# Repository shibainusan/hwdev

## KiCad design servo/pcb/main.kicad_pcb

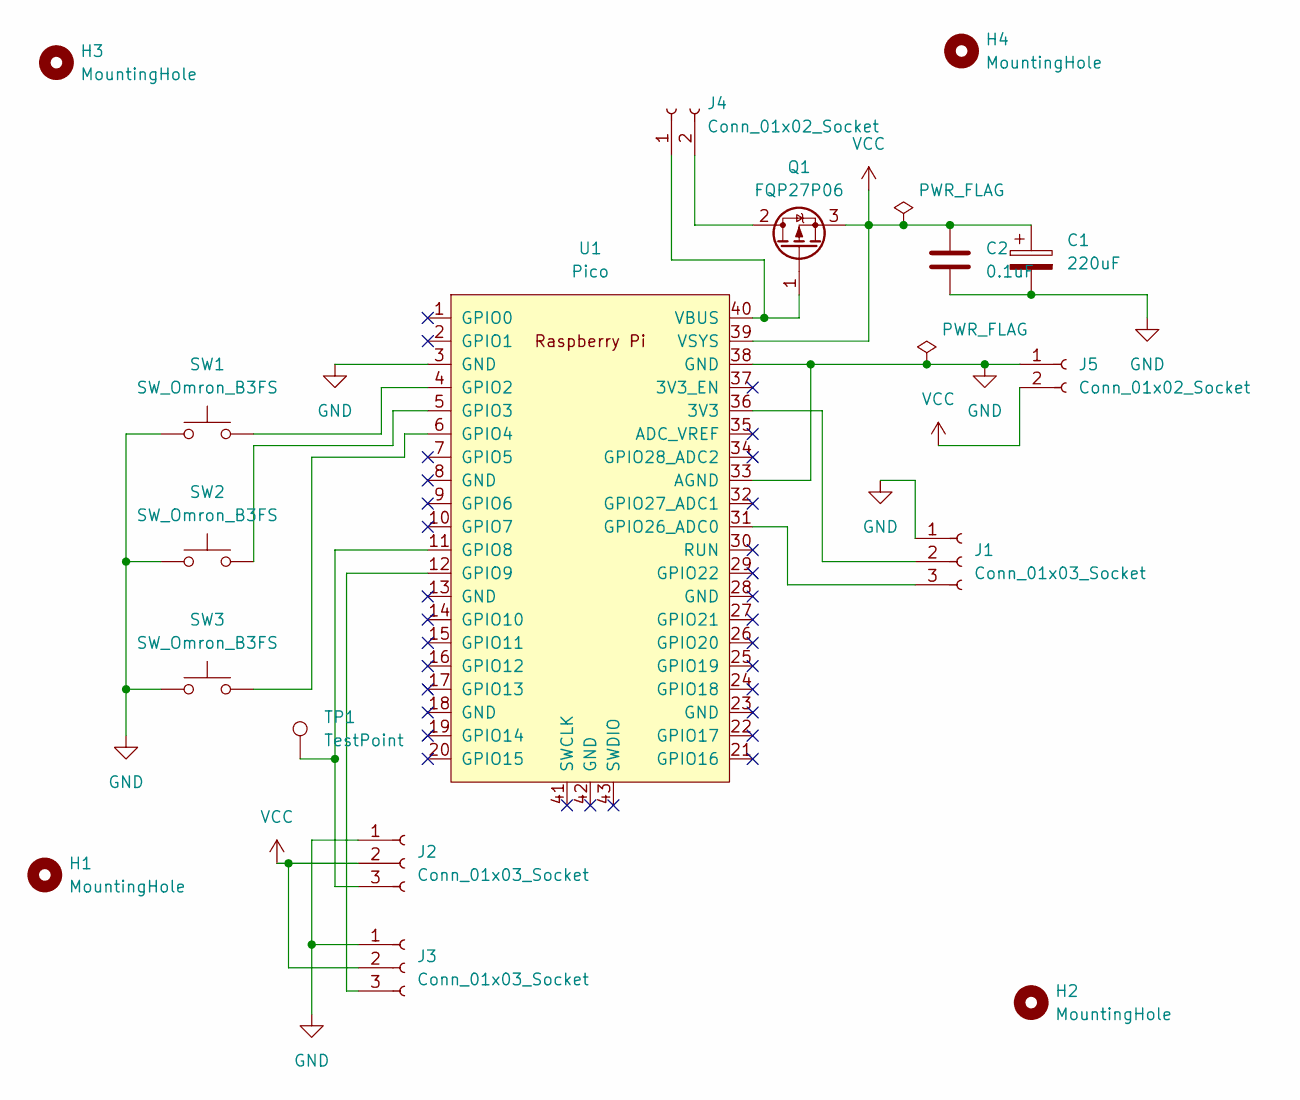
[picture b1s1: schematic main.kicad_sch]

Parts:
C1: 220uF; CP_Radial_D5.0mm_P2.50mm
C2: 0.1uF; C_Disc_D3.0mm_W2.0mm_P2.50mm
H1, H2, H3, H4: MountingHole; MountingHole_3.2mm_M3
J1, J2, J3: Conn_01x03_Socket; PinSocket_1x03_P2.54mm_Vertical
J4, J5: Conn_01x02_Socket; PinSocket_1x02_P2.54mm_Vertical
Q1: FQP27P06; TO-92_Inline_Wide
SW1, SW2, SW3: SW_Omron_B3FS; SW_PUSH_6mm
TP1: TestPoint; TestPoint_THTPad_D2.0mm_Drill1.0mm
U1: Pico; RPi_Pico_SMD_TH

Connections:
GND: C1.2, C2.2, J1.1, J2.1, J3.1, J5.1, SW1.1, SW2.1, SW3.1, U1.3 (GND), U1.33 (AGND), U1.38 (GND)
unnamed: J1.2, U1.36 (3V3)
unnamed: J1.3, U1.31 (GPIO26_ADC0)
unnamed: J2.3, TP1.1, U1.11 (GPIO8)
unnamed: J3.3, U1.12 (GPIO9)
unnamed: J4.1, Q1.1 (G), U1.40 (VBUS)
unnamed: J4.2, Q1.2 (D)
unnamed: SW1.2, U1.4 (GPIO2)
unnamed: SW2.2, U1.5 (GPIO3)
unnamed: SW3.2, U1.6 (GPIO4)
VCC: C1.1, C2.1, J2.2, J3.2, J5.2, Q1.3 (S), U1.39 (VSYS)

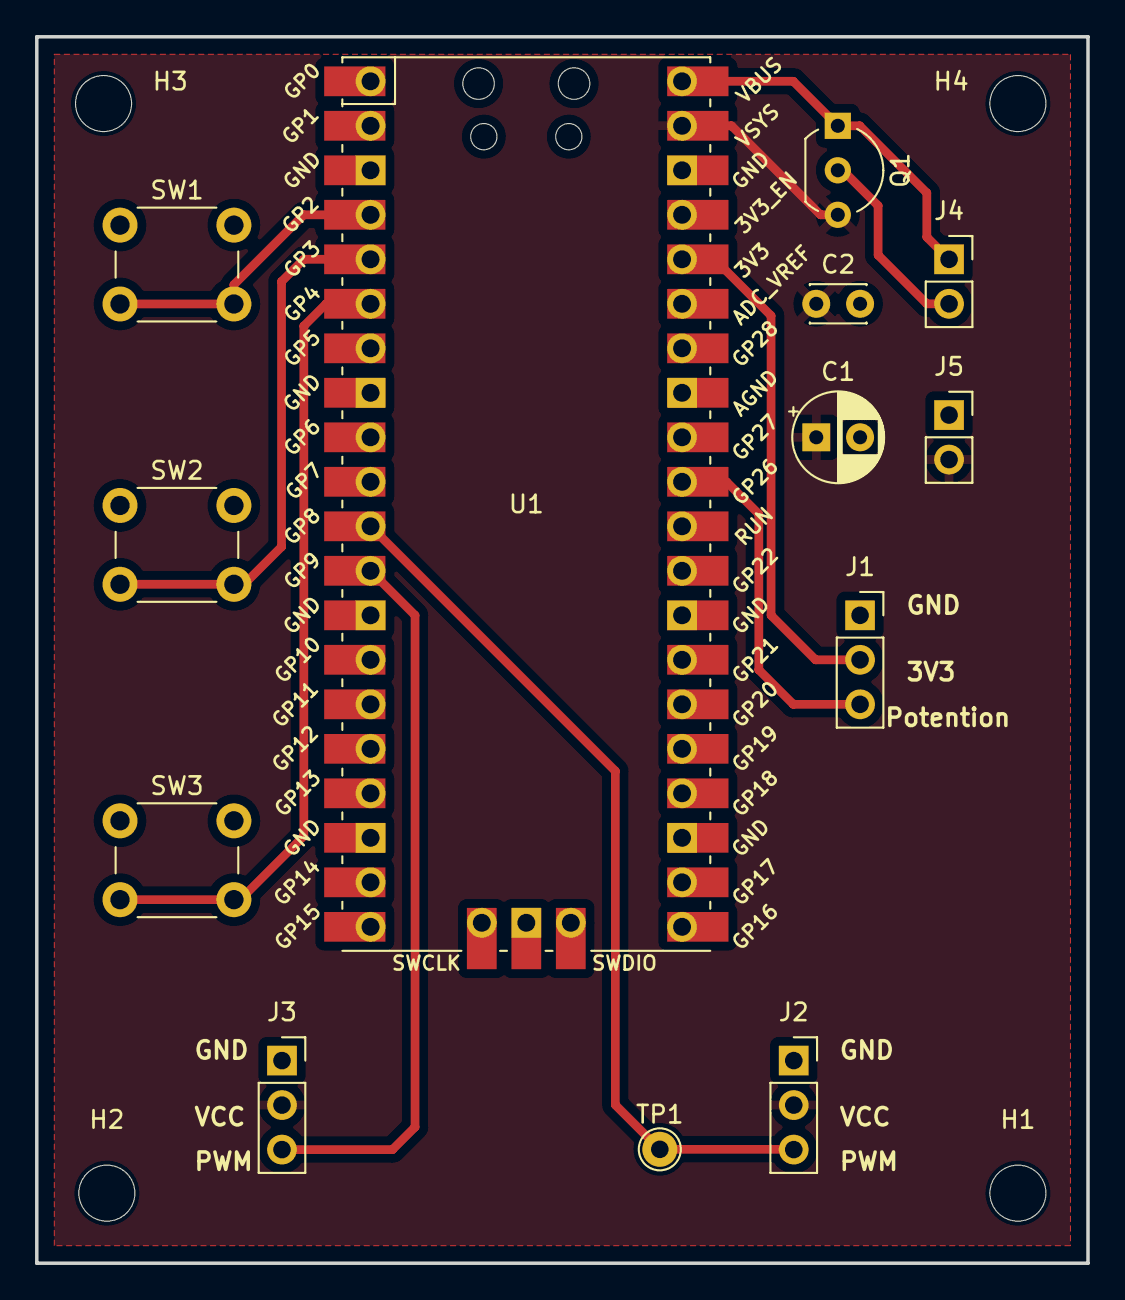
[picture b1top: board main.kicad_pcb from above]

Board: 2 copper layers, 60.0 x 70.0 mm, 17 parts (0 on the bottom side), 11 nets.

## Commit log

2017-05-05 old projects
2017-05-05 usb switcher
2017-05-05 working
2017-05-06 CRLF was not removed correctly.
2017-05-06 1st release
2017-05-06 power source board with 5V and DC-DC stepdown converter output.
2017-06-17 replaced to N MOS FET
2023-11-07 4 port SMA switcher Arduino FW and schematics
2023-11-08 Case
2023-11-09 OpenScad
2023-11-09 https://github.com/BelfrySCAD/BOSL2/archive/refs/heads/master.zip
2023-11-09 Arduino基板が入らないので天井上げ ねじ穴を皿ネジに
2023-11-09 sidepanel
2023-11-11 Portずらし対応
2023-11-18 initial
2023-11-19 高さが10cm超えるので無理やり
2023-11-19 FANねじ止め箇所が浮く問題修正
2023-11-19 back/Front panel長さ調整
2023-11-27 コマンド対応 ファンガードの穴拡大
2023-12-10 穴位置調整
2023-12-14 回転軸のクリアランスが小さすぎて回転が渋い ハウジング内側ねじ穴が回転軸と干渉する サーボ取り付けねじ穴が浅い
2023-12-17 servo軸を直接マウントできないぽい。
2023-12-22 Servoハウジング頭 Servo固定
2023-12-22 シリコン抑え
2023-12-23 サーボ取り付けホイールの真ん中にねじ穴逃げを設置 M2ビスの効きがわるいので受け穴を1.8mm-->1.6mmに縮小
2023-12-25 トップカバー穴あけ
2023-12-27 LR逆回転モード追加
2023-12-28 実体配線簡略化のためにServo制御ピン変更
2023-12-28 操作パネル
2023-12-28 一体成型やめ。面で出して接着する。
2023-12-30 speed選択可能幅拡大
2023-12-31 内部演算を角度センターを0、範囲±90度で計算するようにした
2023-12-31 サーボ直取り付けホーン
2023-12-31 サーボにハマるようになった。ねじはM2。
2024-01-01 attachment受け径拡大。30->32mm
2024-01-01 固定できた
2024-01-01 attachment受け径拡大につきカップ抑えも+2mm拡大
2024-01-06 Controlケースを一体成型とパーツ接着組み立てで分離
2024-01-07 P配線した
2024-01-07 rev1
2024-01-14 足を追加
2024-01-14 Added sleep mode.
2024-01-21 P板むけ変更
2024-01-21 tpuとplaで分けた
2024-01-23 サイズ調整
2024-01-27 added rp2040 dormant mode. https://github.com/matthias-bs/arduino-pico-sleep
2024-02-24 unblock ClientConnectThread
2024-02-24 readable log
2024-02-24 Send WoL Magic packet
2024-02-26 Local TCP sessionが切れると無限ループになる問題修正
2024-02-26 implementing local commands.
2024-02-27 Add local commands
2024-02-27 Leave log when local command was passed.
2024-10-12 enlarge base
2024-10-12 Reduced the height of LED holder.
2024-10-13 Shortened commands.
2024-10-14 Fixed hole positions
